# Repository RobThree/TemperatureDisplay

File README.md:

#  Temperature Display

Uses an Wemos D1 mini with a GXHT30 I²C temperature & humidity sensor and a SSD1306 I²C 0.96" OLED display.

This project supports OTA updates, uses the WiFi manager to configure the WiFi and provides a REST API to get the temperature and humidity as JSON. The readings (and display) are updated every 2 seconds (by default, configurable) and also output to serial.

## Hardware

You'll need:

* [Wemos D1 mini or clone](https://aliexpress.com/w/wholesale-wemos-d1-mini.html)
* [GXHT30 I²C temperature & humidity sensor module](https://aliexpress.com/w/wholesale-GXHT30-module.html)
* [SSD1306 I²C 0.96" OLED display](https://aliexpress.com/w/wholesale-SSD1306-0.96%22.html)
* 2x [2.54mm female header 8 pins](https://aliexpress.com/w/wholesale-2.54mm-female-header-8-pins.html)
* 2x 8 pin and 2x 4 pin [2.54mm pin headers](https://aliexpress.com/w/wholesale-single-row-male-2.54mm.html)

All of these components are readily available at the time of writing, you should be able to easily source them.

### PCB

The [`pcb`](/pcb/) directory contains the KiCad (9.0) design files for the Wemos D1 mini shield PCB. [PCBWay](https://www.pcbway.com/) reached out to me and was kind enough to support this project. The project is available at [PCBWay's Shared Projects](https://www.pcbway.com/project/shareproject/Temperature_display_f0e459fd.html) for easy ordering.

For more pictures of the PCB and/or project see [the project page](https://www.pcbway.com/project/shareproject/Temperature_display_f0e459fd.html) or the [/img/PCBWay](/img/PCBWay/) directory. I would like to thank PCBWay again 🙏 Shipping was incredibly quick 🛫🛬 and the PCB is perfectly finished 👌

In a next iteration I'm hoping to integrate the GXHT30 on the shield, but being pretty new to PCB design this first iteration uses a module.

### DIY

Connect the GXHT30 and SSD1306 to the Wemos D1 mini's `3v3` pin, connect the grounds of all three modules. And connect `SDA` to `D2` (`GPIO4`) and `SCL` to `D1` (`GPIO5`). That's it. Done. Apparently some modules require 5V; if your display is glitching or not turning on, try connecting it to the 5V pin on the Wemos D1 mini. I power the project via the Wemos' onboard USB port but you should also be able to power it by directly powering the power pins.

```
                           +----------+        +------------------+
                           |  GXHT30  |        |     SSD1306      |
                           |    [X]   |        |                  |
                           |          |        |                  |
                           | V G  S S |        |    V  G  S  S    |
   +-----------------+     | C N  D C |        |    C  N  D  C    |
   |  Wemos D1 mini  |     | C D  A L |        |    C  D  A  K    |
   |    (ESP8266)    |     +----------+        +------------------+
   |                 |       | |  | |               |  |  |  |
   |              D1 |-------|-|--|-+---------------|--|--|--+
   |              D2 |-------|-|--+-----------------|--|--+
   |                 |       | |                    |  |
   |                 |       | |                    |  |
   |                 |       | |                    |  |
   |                 |       | |                    |  |
   |             GND |-------|-+--------------------|--+
+--| 3V3             |       |                      |
|  +-----------------+       |                      |
+----------------------------+----------------------+
```

### Tips on assembly:

* ⚠️ On some displays [there's a capacitor that can get quite close to the pins of this board](/img/pin.jpg). You might want to take a sidecutter and snip of a piece of the pin or use some kapton tape or some other means to isolate the pin. Make sure you check BOTH left and right side of the display!
* Solder the pinheaders/sockets **first**, and only **then** solder the display / temperature sensor. If you solder the display first you'll have a hard time reaching the pins connecting the board to the Wemos D1 mini
* When soldering the display to the board, [use a female header as a spacer](/img/spacer.jpg) for the perfect alignment.
* You don't _need_ to use male/female headers to connect the Wemos D1 mini to the PCB, you can use pins-only to make the device more compact. Just make sure you keep enough clearance!
* Don't forget to emjoy the peel-feel when removing the protective peel from the OLED 🤤

## Software

This is a PlatformIO project. I'm sure someone will help convert this to an Arduino IDE project, but it's not going to be me.

### How to get started

1. Open this folder in [PlatformIO for VSCode](https://platformio.org/platformio-ide)
2. Copy [`include/example_config.h`](include/example_config.h) to `include/config.h` and change the OTA update password and **devicename** (this one is optional)
3. Copy [`example_env_secrets.ini`](example_env_secrets.ini) to `env_secrets.ini` and set the same password for the `--auth` option
4. ⚠️ Make sure your [`platformio.ini`](platformio.ini) file has `default_envs` set to `d1_mini_serial`
5. Connect your USB cable to your device and the Wemos D1 mini
6. Compile the project and upload via (USB virtual) serial to your Wemos D1 mini
7. You should now be able to connect to a WiFi AP named after your **devicename** (see step 2); connect to it, set your WiFi credentials and save
8. The Wemos D1 mini should reboot and the OLED display should (shortly) show the IP; the display should show any other errors or problems as well
9. Next time you update you can use the OTA configuration (`default_envs` set to `d1_mini_ota` and the correct IP in `env_secrets.ini` at the `upload_port` entry), no more need for USB cables

### Once it's up and running

The display will show the temperature in °C or Fahrenheit (see `include/config.h`) and the humidity in %RH (Relative Humidity). If your sensor is way off you can fix this by setting `TEMPERATUREOFFSET` and/or `HUMIDITYOFFSET` in `include/config.h` and updating the device or, much easier, by using the web UI. The temperature and humidity will also be output to the serial port every time the sensor is read (see `UPDATEINTERVAL`) and when you use the `/read` endpoint of the REST API (e.g. `http://<deviceip>/read` [`GET`]) you'll get the readings as json:

```json
{
  "celsius": {
    "temperature": 22.81,
    "offset": -5
  },
  "fahrenheit": {
    "temperature": 73.058,
    "offset": -9
  },
  "humidity": {
    "relative_perc": 31.29,
    "relative_perc_offset": 8
  },
  "wifi": {
    "rssi": -48
  },
  "lastupdate": "1.62 seconds ago",
  "display": "c",
  "devicename": "MyDevice"
}
```

These values are only updated every time the sensor is read (again: see `UPDATEINTERVAL`). There is also a `/reset` endpoint ([`PUT`]) that will reboot the device.

Finally, the device also offers a user-friendly UI at the `/` endpoint (e.g. `http://<deivce-ip-here>/`) which updates every 5 seconds:

You can find the settings at `http://<deivce-ip-here>/settings` or by clicking the cog in the top right corner of the home screen. The settings screen allows you to adjust some values. Once your changed settings have been saved you can go back home by clicking the 'home' icon in the top right corner.

## Attribution

* PCB design based based on [Jérôme Labidurie](https://github.com/jerome-labidurie)'s [Wemos D1 mini Shield template for KiCad](https://github.com/jerome-labidurie/d1_mini_kicad)
* Logo from [SVG Repo](https://www.svgrepo.com/svg/179515/thermometer-temperature) (CC0 License)

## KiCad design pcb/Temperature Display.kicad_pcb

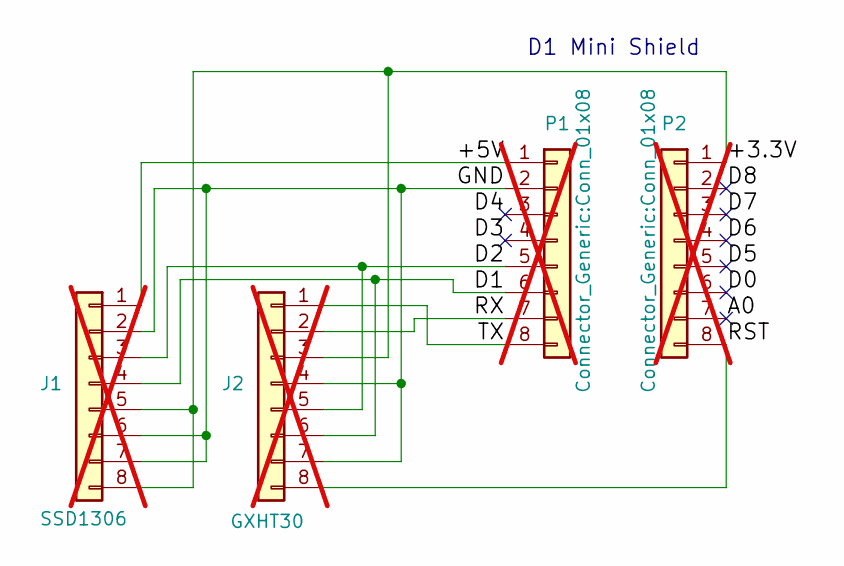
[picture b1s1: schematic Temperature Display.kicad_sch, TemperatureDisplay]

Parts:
J1: SSD1306; PinHeader_1x08_P2.54mm_Vertical; not fitted
J2: GXHT30; PinHeader_1x08_P2.54mm_Vertical; not fitted
P1, P2: Connector_Generic:Conn_01x08; PinHeader_1x08_P2.54mm_Vertical; not fitted

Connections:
/+3.3V: J1.5, J1.8, J2.3, P2.1
/+5V: J1.1, P1.1
/A0: P2.7
/D0: P2.6
/D1: J1.4, J2.6, P1.6
/D2: J1.3, J2.5, P1.5
/D3: P1.4
/D4: P1.3
/D5: P2.5
/D6: P2.4
/D7: P2.3
/D8: P2.2
/GND: J1.2, J1.6, J1.7, J2.4, J2.7, P1.2
/RST: J2.8, P2.8
/RX: J2.2, P1.7
/TX: J2.1, P1.8

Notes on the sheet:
D1 Mini Shield

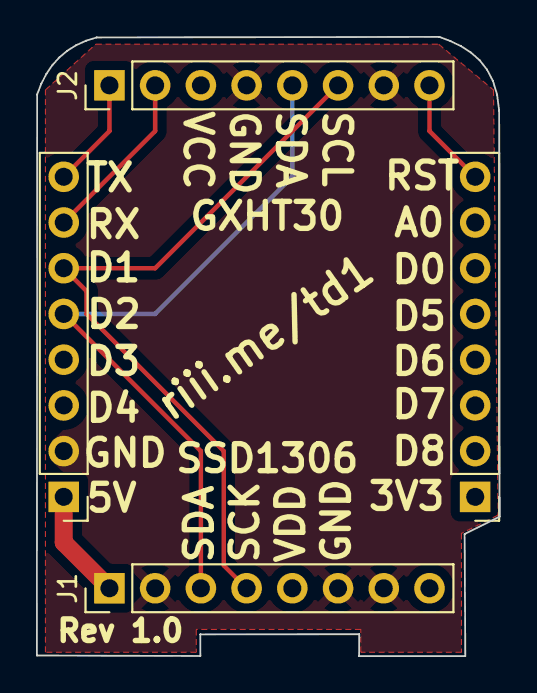
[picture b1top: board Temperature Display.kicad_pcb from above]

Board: 2 copper layers, 25.7 x 34.4 mm, 4 parts (0 on the bottom side), 8 nets.

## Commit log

2025-03-20 Provide "Serial" and "OTA" configs. And wiring schema.
2025-03-25 Added KiCad PCB design
2025-03-25 Added links to components.
2025-03-25 PCB cleanup / optimization and silkscreen adjustments
2025-03-25 Update README, added software chapter, add PCB images.
2025-03-25 Update README introduction
2025-03-25 Typo 🤦‍♂️
2025-03-26 More PCB optimization, minor README fixes
2025-03-26 Final rev 1.0, ordered at PCBWay
2025-03-31 Cleanup. Add RSSI to json. PCB is blue.
2025-04-02 Add license
2025-04-02 Update license
2025-04-02 Add humidity offset. Cleaned up JSON response. Add option to show Fahrenheit on display.
2025-04-02 Update README. Add fahrenheit value to serial output.
2025-04-03 Fix bug in fahrenheit offset calculation.
2025-04-03 Added photos of actual PCB by PCBWay.
2025-04-03 Fix spelling
2025-04-03 Add tiny simple web ui
2025-04-03 Add web UI screenshot to README
2025-04-03 Add settings interface
2025-04-03 Cleanup & refactor. Add caching header.
2025-04-04 Added helptext, fixed secondary button hover highlight.
2025-04-04 Remove old logo
2025-04-04 Added assembly tips
2025-04-04 Added another tip.
2025-04-07 Fix variablename
2025-04-09 Move stuff to separate files
2025-04-09 More splitting to separate files
2025-04-09 Format documents
2025-04-09 More cleanup
2025-04-09 Proper naming for private variables
2025-04-09 Better naming
2025-04-09 Fix some C/F confusion introduced by CoPilot
2025-04-09 Minor cleanup & refactoring
2025-04-09 Cleanup HTML, add spinner on settingspage while loading settings
2025-04-09 Properly initialize display
2025-04-09 More status on display
2025-04-09 Refactor and organize code structure (#1)
    * Move stuff to separate files
    * More splitting to separate files
    * Format documents
    * More cleanup
    * Proper naming for private variables
    * Better naming
2025-04-09 Reformatting
2025-04-09 Update clang-format
2025-04-09 Added /mac endpoint
2025-04-09 Move filesystem begin to webserver constructor
2025-04-11 Maxlength was off by one
2025-04-14 Number inputs are less wide
